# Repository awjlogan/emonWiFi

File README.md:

# emonWiFi

A small adapter to fit on Raspberry Pi header. This exposes:

- UART
- 5V

to the ESP32-C3.

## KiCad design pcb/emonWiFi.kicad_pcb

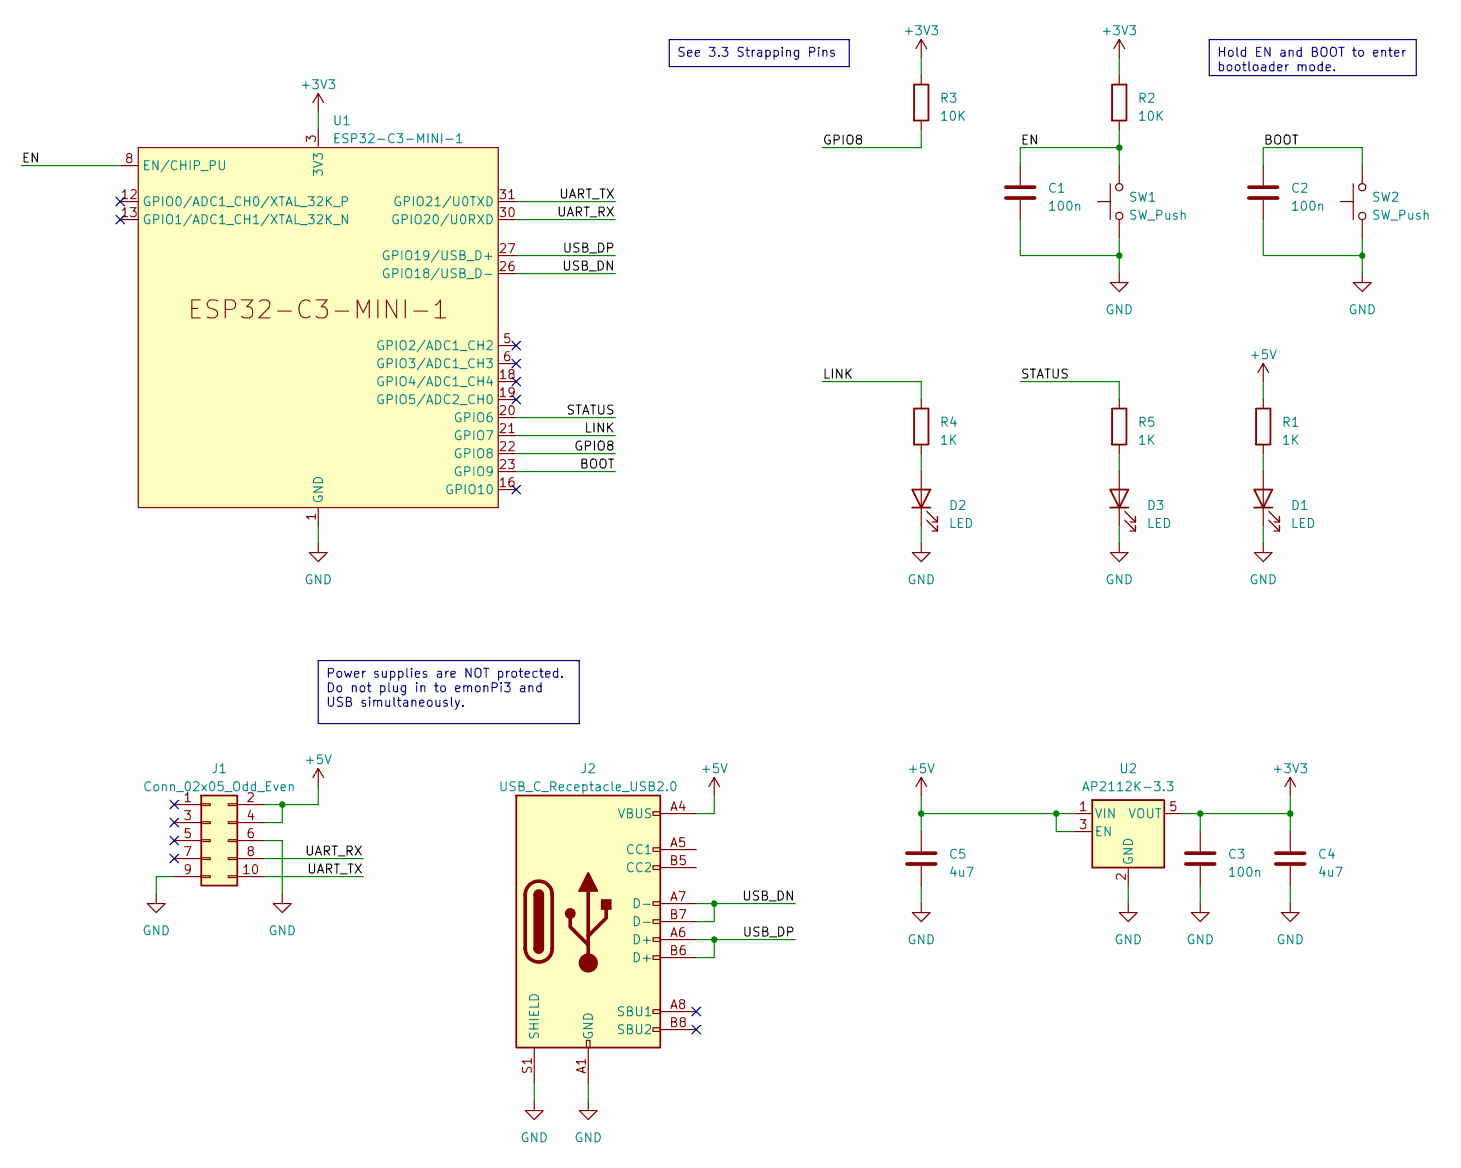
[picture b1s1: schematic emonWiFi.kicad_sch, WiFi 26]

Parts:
C1, C2, C3: 100n; C_0603_1608Metric
C4, C5: 4u7; C_0603_1608Metric
D1, D2, D3: LED; LED_0805_2012Metric
J1: Conn_02x05_Odd_Even; PinHeader_2x05_P2.54mm_Vertical
J2: USB_C_Receptacle_USB2.0; CSP-USC16-TR
R1, R4, R5: 1K; R_0603_1608Metric
R2, R3: 10K; R_0603_1608Metric
SW1, SW2: SW_Push; SW_Tactile_SPST_NO_Straight_CK_PTS636Sx25SMTRLFS
U1: ESP32-C3-MINI-1
U2: AP2112K-3.3; SOT-23-5

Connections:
+3V3: C3.1, C4.1, R2.1, R3.1, U1.3 (3V3), U2.5 (VOUT)
+5V: C5.1, J1.2, J1.4, J2.A4 (VBUS), J2.A9 (VBUS), J2.B4 (VBUS), J2.B9 (VBUS), R1.1, U2.1 (VIN), U2.3 (EN)
/BOOT: C2.1, SW2.2, U1.23 (GPIO9)
/EN: C1.1, R2.2, SW1.2, U1.8 (EN/CHIP_PU)
/GPIO8: R3.2, U1.22 (GPIO8)
/LINK: R4.1, U1.21 (GPIO7)
/STATUS: R5.1, U1.20 (GPIO6)
/UART_RX: J1.8, U1.30 (GPIO20/U0RXD)
/UART_TX: J1.10, U1.31 (GPIO21/U0TXD)
/USB_DN: J2.A7 (D-), J2.B7 (D-), U1.26 (GPIO18/USB_D-)
/USB_DP: J2.A6 (D+), J2.B6 (D+), U1.27 (GPIO19/USB_D+)
GND: C1.2, C2.2, C3.2, C4.2, C5.2, D1.1 (K), D2.1 (K), D3.1 (K), J1.6, J1.9, J2.A1 (GND), J2.A12 (GND), J2.B1 (GND), J2.B12 (GND), J2.S1 (SHIELD), SW1.1, SW2.1, U1.1 (GND), U1.2 (GND), U1.11 (GND), U1.14 (GND), U1.36 (GND), U1.37 (GND), U1.38 (GND), U1.39 (GND), U1.40 (GND), U1.41 (GND), U1.42 (GND), U1.43 (GND), U1.44 (GND), U1.45 (GND), U1.46 (GND), U1.47 (GND), U1.48 (GND), U1.49 (GND), U1.50 (GND), U1.51 (GND), U1.52 (GND), U1.53 (GND), U2.2 (GND)
unnamed: D1.2 (A), R1.2
unnamed: D2.2 (A), R4.2
unnamed: D3.2 (A), R5.2

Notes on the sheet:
Power supplies are NOT protected. Do not plug in to emonPi3 and USB simultaneously.
Hold EN and BOOT to enter bootloader mode.
See 3.3 Strapping Pins

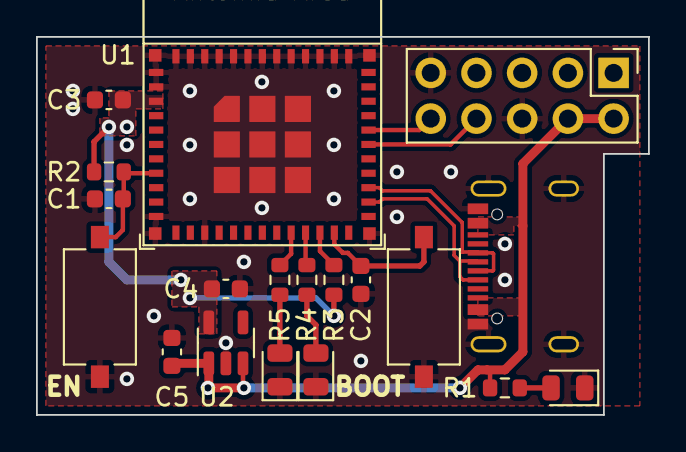
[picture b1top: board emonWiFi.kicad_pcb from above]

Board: 2 copper layers, 34.0 x 21.0 mm, 19 parts (0 on the bottom side), 15 nets.
